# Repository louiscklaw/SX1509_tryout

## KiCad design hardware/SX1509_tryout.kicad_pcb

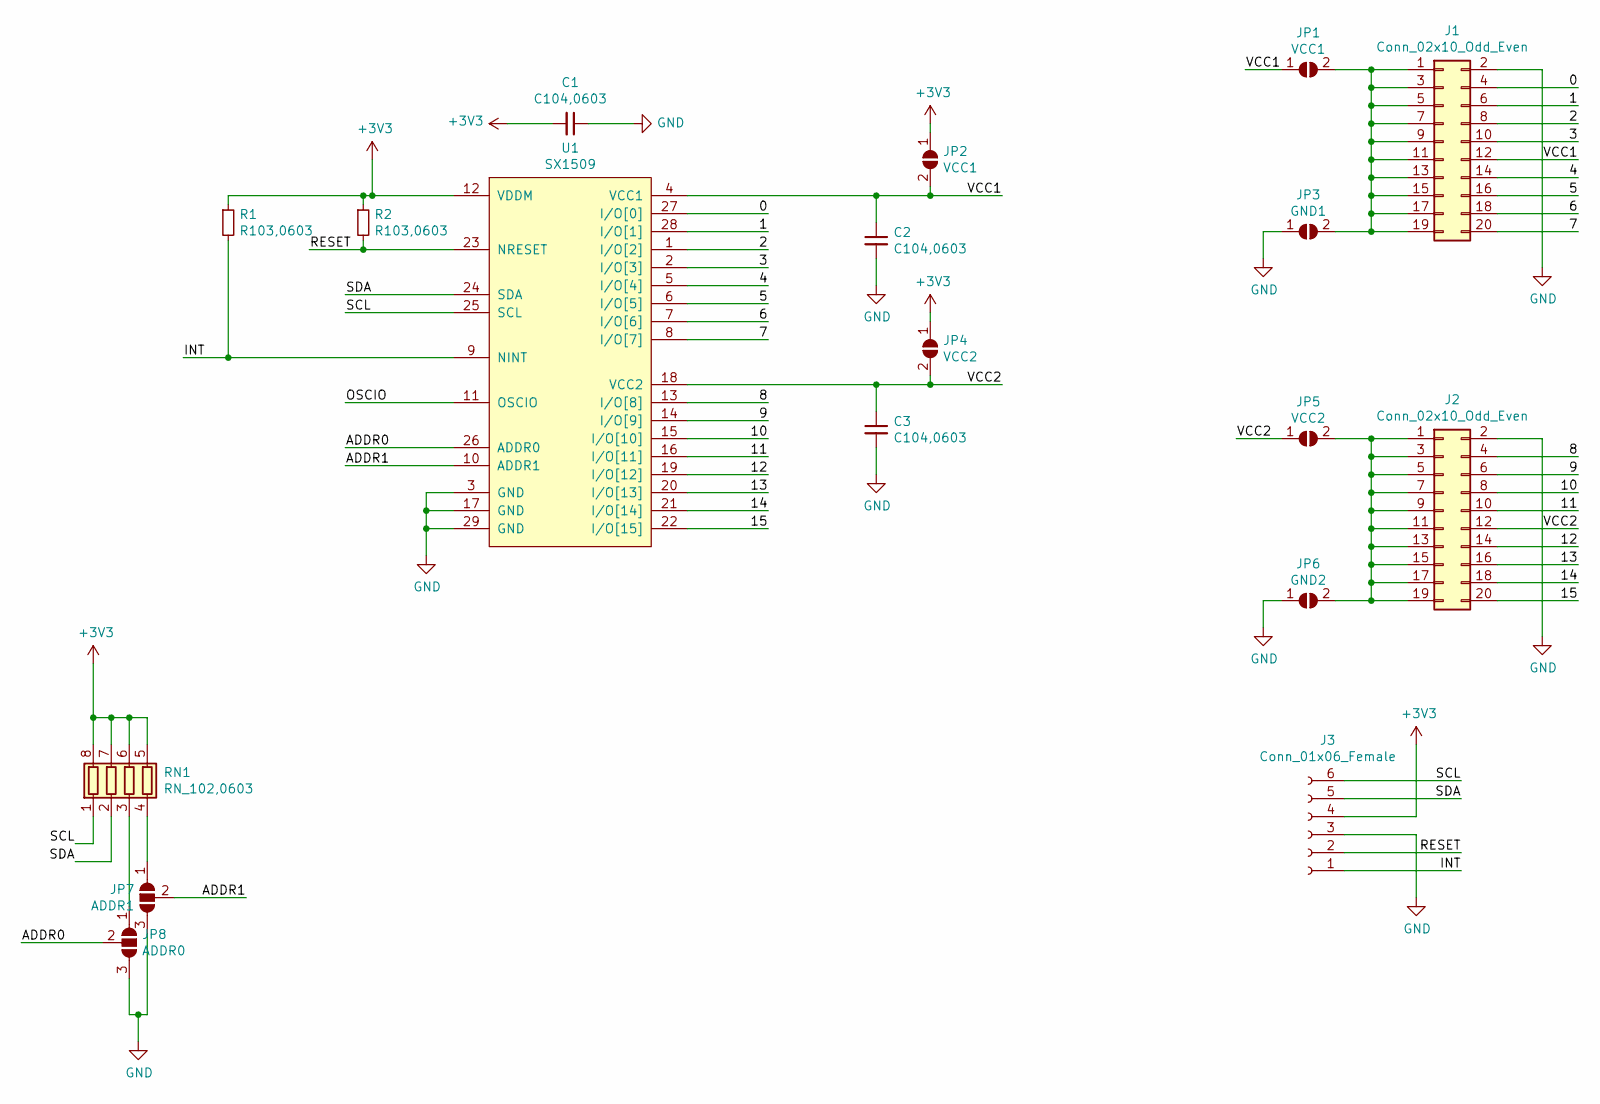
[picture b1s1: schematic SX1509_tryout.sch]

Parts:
C1, C2, C3: C104,0603; C_0603_1608Metric_Pad1.05x0.95mm_HandSolder
J1, J2: Conn_02x10_Odd_Even; PinSocket_2x10_P2.54mm_Vertical
J3: Conn_01x06_Female; PinSocket_1x06_P2.54mm_Vertical
JP1: VCC1; SolderJumper-2_P1.3mm_Open_RoundedPad1.0x1.5mm
JP2: VCC1; SolderJumper-2_P1.3mm_Open_TrianglePad1.0x1.5mm
JP3: GND1; SolderJumper-2_P1.3mm_Open_RoundedPad1.0x1.5mm
JP4: VCC2; SolderJumper-2_P1.3mm_Open_TrianglePad1.0x1.5mm
JP5: VCC2; SolderJumper-2_P1.3mm_Open_RoundedPad1.0x1.5mm
JP6: GND2; SolderJumper-2_P1.3mm_Open_RoundedPad1.0x1.5mm
JP7: ADDR1; SolderJumper-3_P2.0mm_Open_TrianglePad1.0x1.5mm_NumberLabels
JP8: ADDR0; SolderJumper-3_P2.0mm_Open_TrianglePad1.0x1.5mm_NumberLabels
R1, R2: R103,0603; R_0603_1608Metric_Pad1.05x0.95mm_HandSolder
RN1: RN_102,0603; R_Array_Concave_4x0603
U1: SX1509

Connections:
+3V3: C1.2, J3.4, JP2.1 (A), JP4.1 (A), R1.1, R2.1, RN1.5 (R4.2), RN1.6 (R3.2), RN1.7 (R2.2), RN1.8 (R1.2), U1.12 (VDDM)
/0: J1.4, U1.27 (I/O[0])
/1: J1.6, U1.28 (I/O[1])
/2: J1.8, U1.1 (I/O[2])
/3: J1.10, U1.2 (I/O[3])
/4: J1.14, U1.5 (I/O[4])
/5: J1.16, U1.6 (I/O[5])
/6: J1.18, U1.7 (I/O[6])
/7: J1.20, U1.8 (I/O[7])
/8: J2.4, U1.13 (I/O[8])
/9: J2.6, U1.14 (I/O[9])
/10: J2.8, U1.15 (I/O[10])
/11: J2.10, U1.16 (I/O[11])
/12: J2.14, U1.19 (I/O[12])
/13: J2.16, U1.20 (I/O[13])
/14: J2.18, U1.21 (I/O[14])
/15: J2.20, U1.22 (I/O[15])
/ADDR0: JP8.2 (C), U1.26 (ADDR0)
/ADDR1: JP7.2 (C), U1.10 (ADDR1)
/INT: J3.1, R1.2, U1.9 (NINT)
/RESET: J3.2, R2.2, U1.23 (NRESET)
/SCL: J3.6, RN1.1 (R1.1), U1.25 (SCL)
/SDA: J3.5, RN1.2 (R2.1), U1.24 (SDA)
/VCC1: C2.1, J1.12, JP1.1 (A), JP2.2 (B), U1.4 (VCC1)
/VCC2: C3.1, J2.12, JP4.2 (B), JP5.1 (A), U1.18 (VCC2)
GND: C1.1, C2.2, C3.2, J1.2, J2.2, J3.3, JP3.1 (A), JP6.1 (A), JP7.3 (B), JP8.3 (B), U1.3 (GND), U1.17 (GND), U1.29 (GND)
unnamed: J1.1, J1.3, J1.5, J1.7, J1.9, J1.11, J1.13, J1.15, J1.17, J1.19, JP1.2 (B), JP3.2 (B)
unnamed: J2.1, J2.3, J2.5, J2.7, J2.9, J2.11, J2.13, J2.15, J2.17, J2.19, JP5.2 (B), JP6.2 (B)
unnamed: JP7.1 (A), RN1.4 (R4.1)
unnamed: JP8.1 (A), RN1.3 (R3.1)

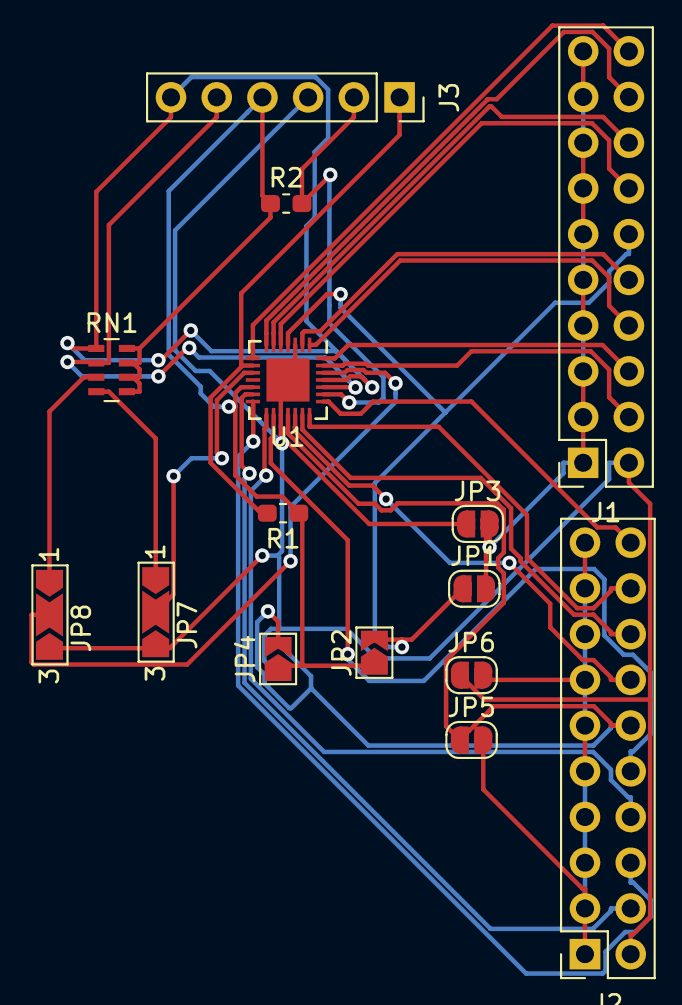
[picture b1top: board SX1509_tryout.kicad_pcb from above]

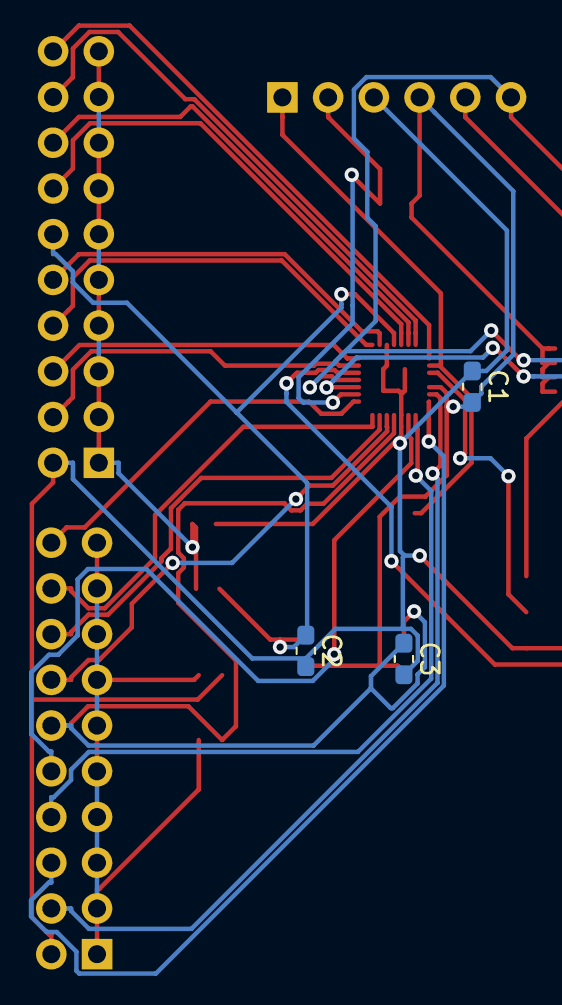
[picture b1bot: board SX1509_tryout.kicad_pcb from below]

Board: 2 copper layers, 18 parts (3 on the bottom side), 30 nets.

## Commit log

2019-07-13 init commit,
2019-07-13 update,
2020-05-05 ci: init travis token,
2020-05-05 ci: init travis build config,
